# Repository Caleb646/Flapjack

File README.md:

# 🥞 Flapjack

Flapjack is a **VTOL drone platform** built from the ground up — custom **airframe**, **PCB**, and **firmware**.
---

## Features

- **Custom Flight Controller PCB**
    - STM32 microcontroller
    - IMU (SPI), barometer, GPS, and compass
    - Servo and ESC outputs

- **Firmware**
    - Python GUI for flight data
    - Real-time flight control loop
    - Sensor fusion (IMU + barometer + compass)
    - PID control
    - PID Mixing for tilt-thrust VTOL (motor + servo)

- **Airframe**
    - Dual-motor VTOL design with tilt servos
    - Lightweight and modular construction
    - Designed for hover-to-cruise transitions

---

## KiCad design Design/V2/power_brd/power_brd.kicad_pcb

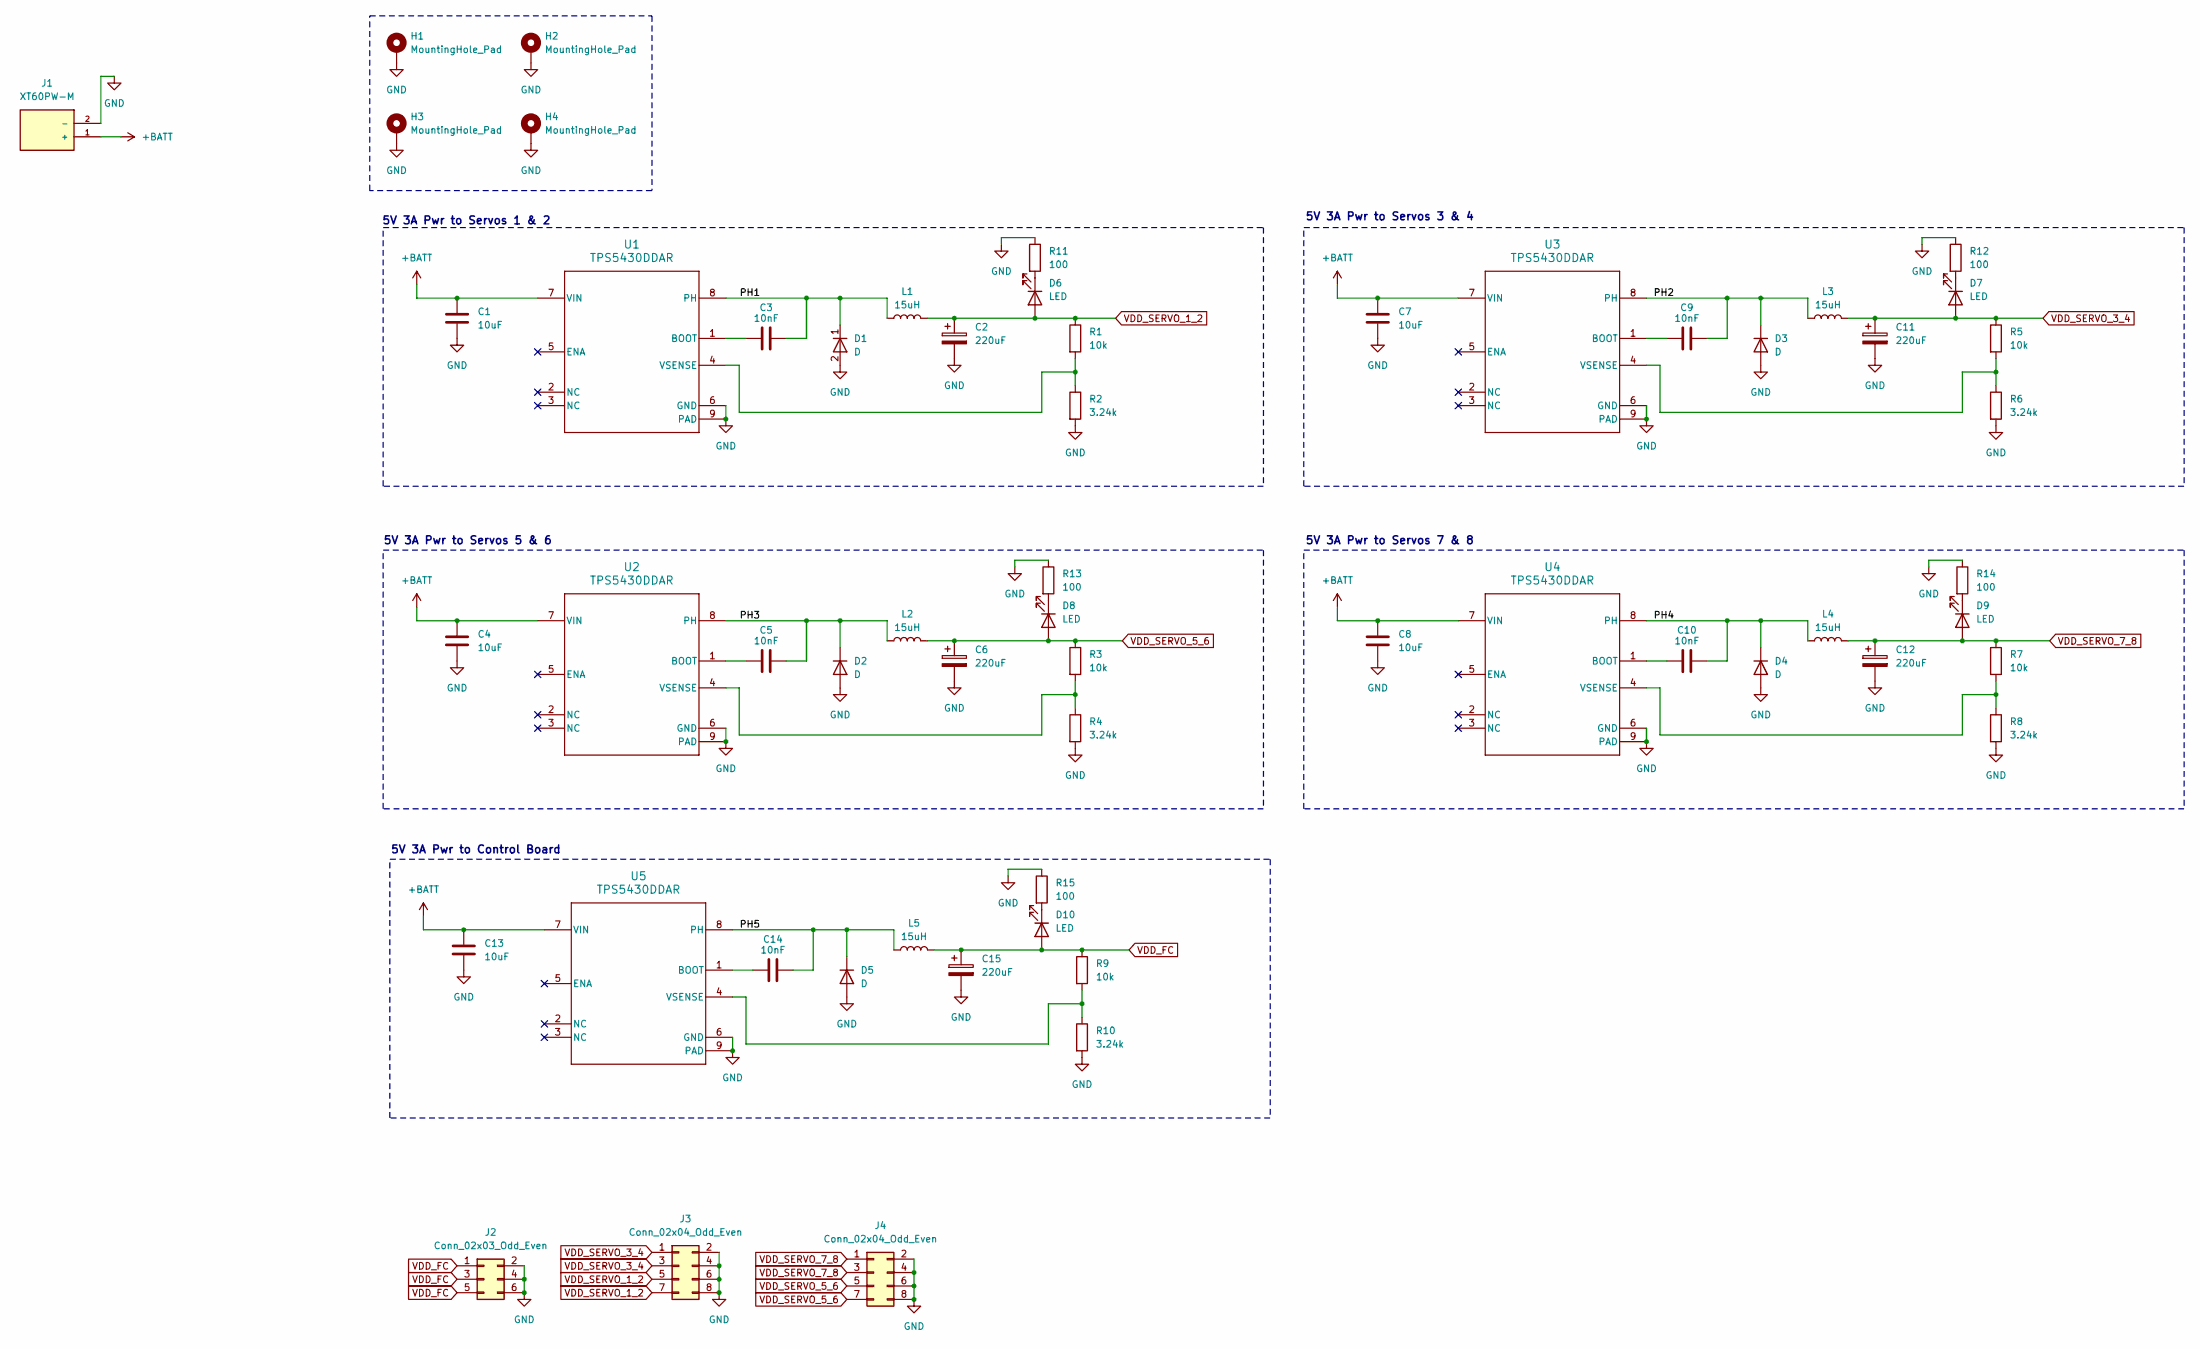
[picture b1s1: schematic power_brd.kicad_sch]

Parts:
C1, C4, C7, C8, C13: 10uF; C_1206_3216Metric_Pad1.33x1.80mm_HandSolder; LCSC Part # C13585
C2, C6, C11, C12, C15: 220uF; 10TPE220ML; LCSC Part # C147767
C3, C5, C9, C10, C14: 10nF; C_0805_2012Metric_Pad1.18x1.45mm_HandSolder; LCSC Part # C1710
D1, D2, D3, D4, D5: D; SMA_L4.3-W2.6-LS5.2-RD; LCSC Part # C8678
D6, D7, D8, D9, D10: LED; LED_0805_2012Metric_Pad1.15x1.40mm_HandSolder; LCSC Part # C84256
H1, H2, H3, H4: MountingHole_Pad; MountingHole_3.2mm_M3_Pad_Via
J1: XT60PW-M
J2: Conn_02x03_Odd_Even; PinHeader_2x03_P2.54mm_Vertical
J3, J4: Conn_02x04_Odd_Even; PinHeader_2x04_P2.54mm_Vertical
L1, L2, L3, L4, L5: 15uH; IND-SMD_L7.1-W6.6; LCSC Part # C22463824
R1, R3, R5, R7, R9: 10k; R_0805_2012Metric_Pad1.20x1.40mm_HandSolder; LCSC Part # C17414
R2, R4, R6, R8, R10: 3.24k; R_0805_2012Metric_Pad1.20x1.40mm_HandSolder; LCSC Part # C17609
R11, R12, R13, R14, R15: 100; R_0805_2012Metric_Pad1.20x1.40mm_HandSolder; LCSC Part # C17408
U1, U2, U3, U4, U5: TPS5430DDAR; LCSC Part # C9864

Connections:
+BATT: C1.1, C4.1, C7.1, C8.1, C13.1, J1.1 (+), U1.7 (VIN), U2.7 (VIN), U3.7 (VIN), U4.7 (VIN), U5.7 (VIN)
/PH1: C3.2, D1.1 (K), L1.1, U1.8 (PH)
/PH2: C9.2, D3.1 (K), L3.1, U3.8 (PH)
/PH3: C5.2, D2.1 (K), L2.1, U2.8 (PH)
/PH4: C10.2, D4.1 (K), L4.1, U4.8 (PH)
/PH5: C14.2, D5.1 (K), L5.1, U5.8 (PH)
GND: C1.2, C2.2, C4.2, C6.2, C7.2, C8.2, C11.2, C12.2, C13.2, C15.2, D1.2 (A), D2.2 (A), D3.2 (A), D4.2 (A), D5.2 (A), H1.1, H2.1, H3.1, H4.1, J1.2 (-), J2.2, J2.4, J2.6, J3.2, J3.4, J3.6, J3.8, J4.2, J4.4, J4.6, J4.8, R2.2, R4.2, R6.2, R8.2, R10.2, R11.1, R12.1, R13.1, R14.1, R15.1, U1.6 (GND), U1.9 (PAD), U2.6 (GND), U2.9 (PAD), U3.6 (GND), U3.9 (PAD), U4.6 (GND), U4.9 (PAD), U5.6 (GND), U5.9 (PAD)
unnamed: D6.1 (K), R11.2
unnamed: D7.1 (K), R12.2
unnamed: D8.1 (K), R13.2
unnamed: D9.1 (K), R14.2
unnamed: D10.1 (K), R15.2
unnamed: C3.1, U1.1 (BOOT)
unnamed: R1.2, R2.1, U1.4 (VSENSE)
unnamed: C5.1, U2.1 (BOOT)
unnamed: R3.2, R4.1, U2.4 (VSENSE)
unnamed: C9.1, U3.1 (BOOT)
unnamed: R5.2, R6.1, U3.4 (VSENSE)
unnamed: C10.1, U4.1 (BOOT)
unnamed: R7.2, R8.1, U4.4 (VSENSE)
unnamed: C14.1, U5.1 (BOOT)
unnamed: R9.2, R10.1, U5.4 (VSENSE)
VDD_FC: C15.1, D10.2 (A), J2.1, J2.3, J2.5, L5.2, R9.1
VDD_SERVO_1_2: C2.1, D6.2 (A), J3.5, J3.7, L1.2, R1.1
VDD_SERVO_3_4: C11.1, D7.2 (A), J3.1, J3.3, L3.2, R5.1
VDD_SERVO_5_6: C6.1, D8.2 (A), J4.5, J4.7, L2.2, R3.1
VDD_SERVO_7_8: C12.1, D9.2 (A), J4.1, J4.3, L4.2, R7.1

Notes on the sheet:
5V 3A Pwr to Servos 3 & 4
5V 3A Pwr to Servos 7 & 8
5V 3A Pwr to Servos 5 & 6
5V 3A Pwr to Servos 1 & 2
5V 3A Pwr to Control Board

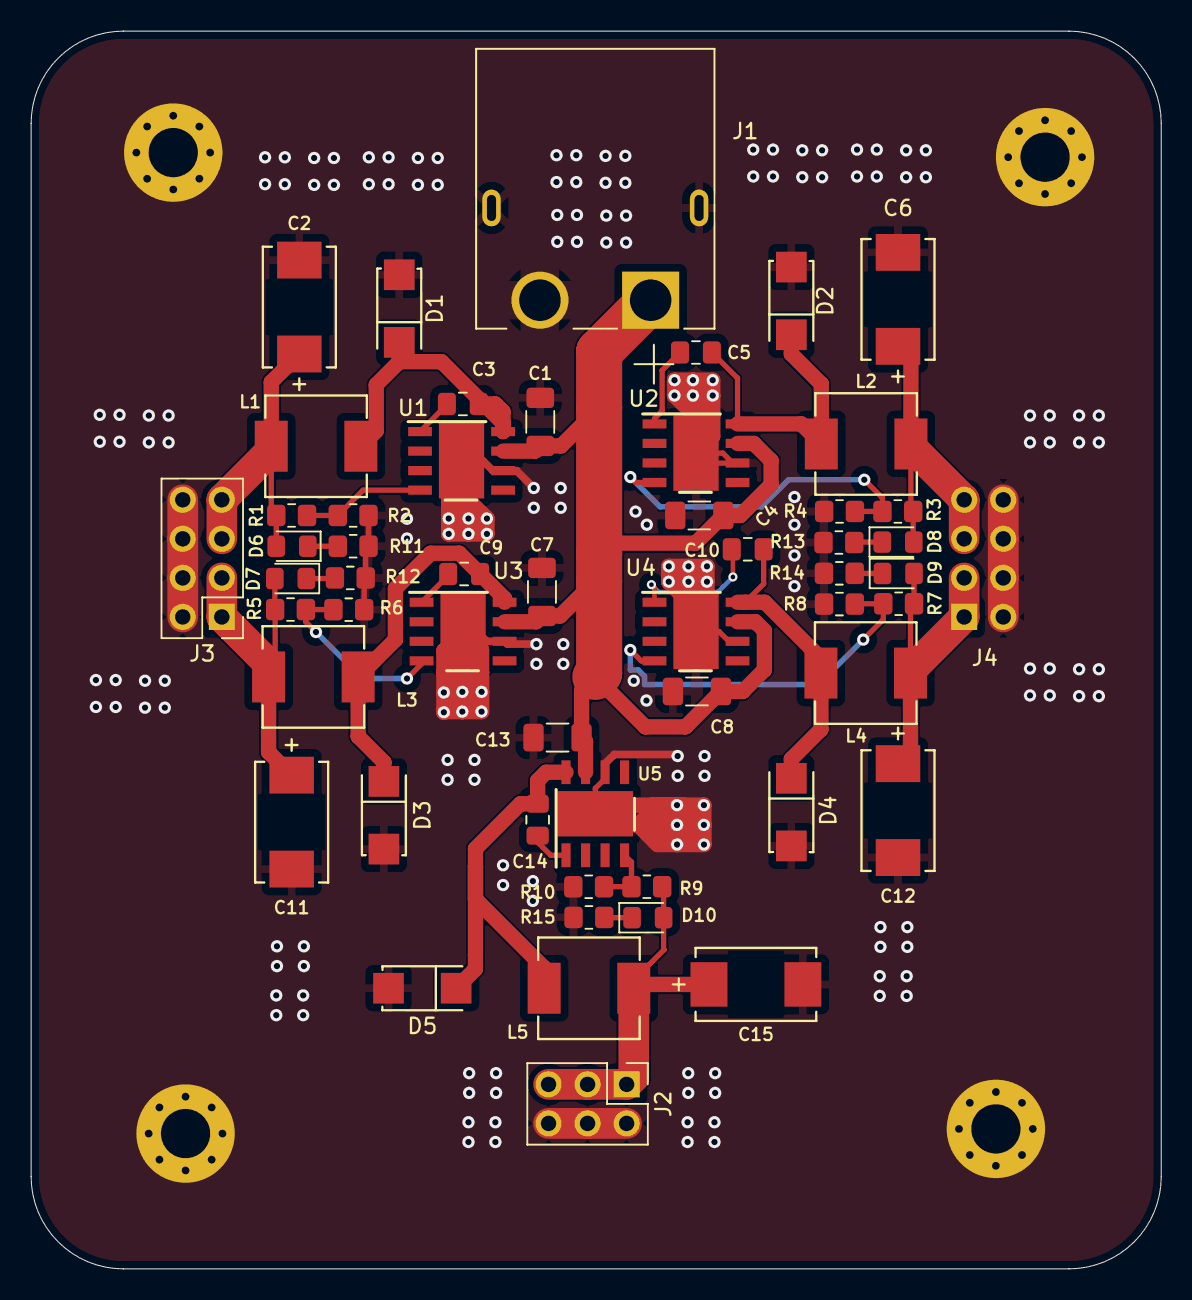
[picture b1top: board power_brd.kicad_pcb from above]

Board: 4 copper layers, 73.5 x 80.5 mm, 58 parts (1 on the bottom side), 27 nets.

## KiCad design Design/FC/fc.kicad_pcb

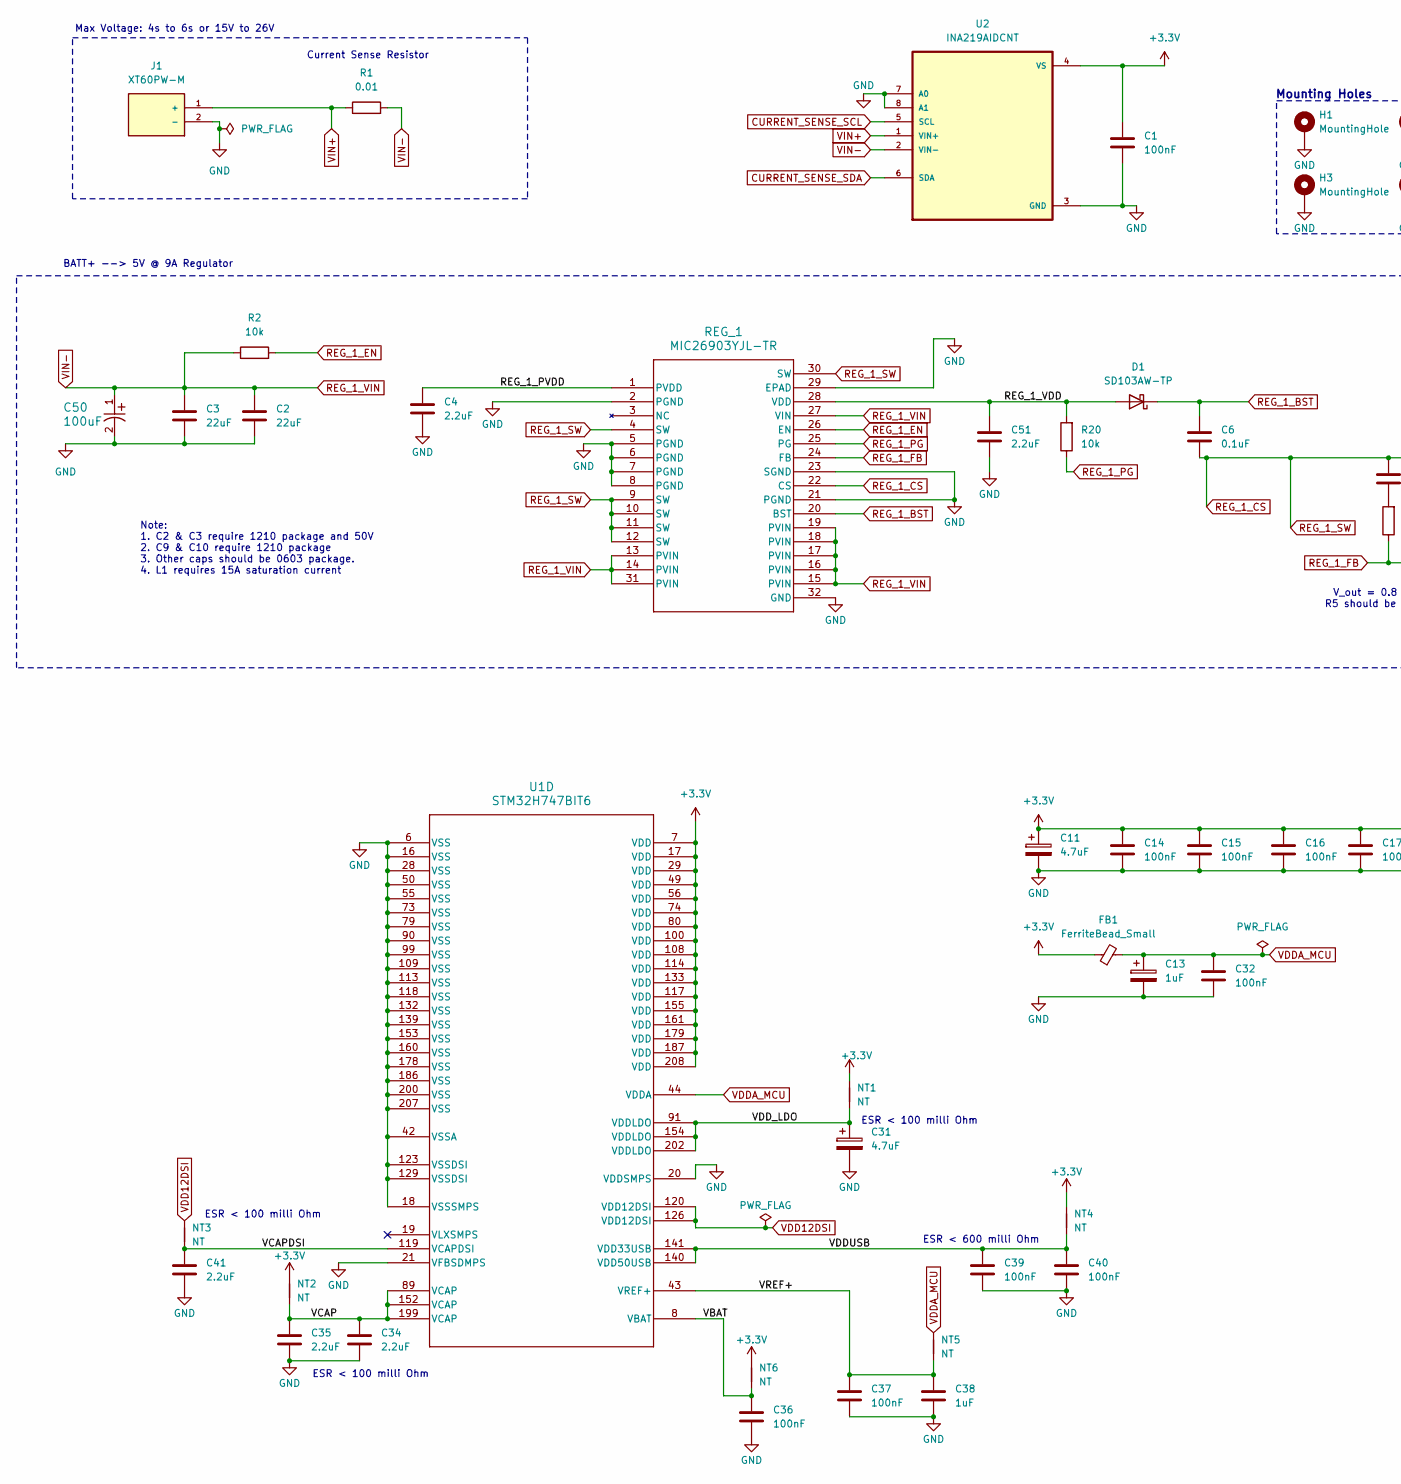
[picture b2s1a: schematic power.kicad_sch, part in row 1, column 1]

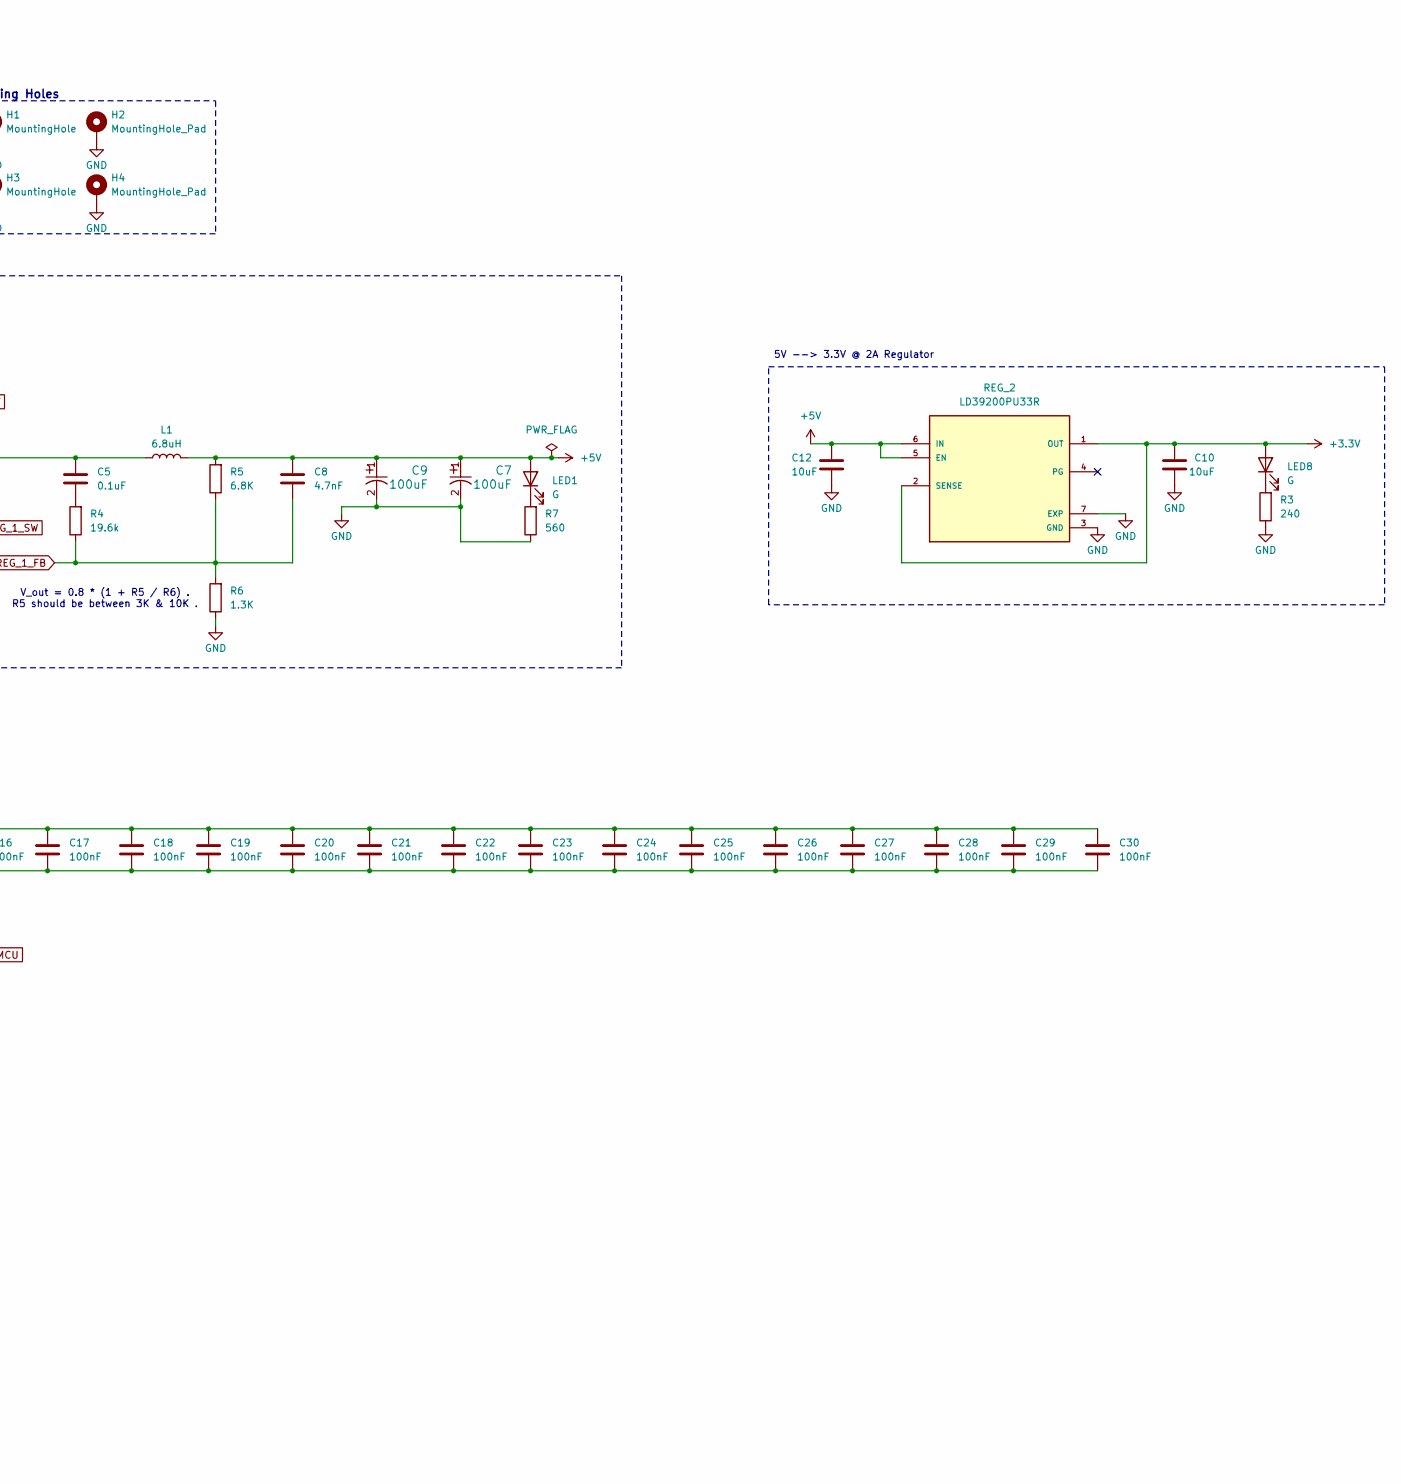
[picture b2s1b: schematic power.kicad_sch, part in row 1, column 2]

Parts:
C1, C14, C15, C16, C17, C18, C19, C20, C21, C22, C23, C24, C25, C26, C27, C28, C29, C30, C32, C36, C37, C39, C40: 100nF; C_0603_1608Metric_Pad1.08x0.95mm_HandSolder; Manufacturer_Part_Number CC0603KRX7R7BB104
C2, C3: 22uF; C_1210_3225Metric_Pad1.33x2.70mm_HandSolder; Manufacturer_Part_Number MSASG32MSB5226MPNA01
C4, C51: 2.2uF; C_0805_2012Metric_Pad1.18x1.45mm_HandSolder; Manufacturer_Part_Number UMK212BB7225KG-T
C5, C6: 0.1uF; C_0805_2012Metric_Pad1.18x1.45mm_HandSolder; Manufacturer_Part_Number KGM21NR71H104KT
C7, C9, C50: 100uF; CAP_6.3 X 7.7_PAN; Manufacturer_Part_Number EEE-FPV101XAP
C8: 4.7nF; C_0805_2012Metric_Pad1.18x1.45mm_HandSolder; Manufacturer_Part_Number C0805C472J3GEC7210
C10, C12: 10uF; C_0603_1608Metric_Pad1.08x0.95mm_HandSolder; Manufacturer_Part_Number GRM188R61E106KA73D
C11, C31: 4.7uF; C_0603_1608Metric_Pad1.08x0.95mm_HandSolder; Manufacturer_Part_Number GRM188R61E475KE11D
C13: 1uF; C_0603_1608Metric_Pad1.08x0.95mm_HandSolder; Manufacturer_Part_Number TACL105K016RTA
C34, C35, C41: 2.2uF; C_0603_1608Metric_Pad1.08x0.95mm_HandSolder; Manufacturer_Part_Number TMK107ABJ225KA-T
C38: 1uF; C_0603_1608Metric_Pad1.08x0.95mm_HandSolder; Manufacturer_Part_Number GRM188R61A105KA61D
D1: SD103AW-TP; Nexperia_CFP3_SOD-123W; Manufacturer_Part_Number SD103AW-TP
FB1: FerriteBead_Small; MPZ1005S121HT000; Manufacturer_Part_Number MPZ1005S121HT000
H1, H3: MountingHole; MountingHole_3.2mm_M3_Pad_Via
H2, H4: MountingHole_Pad; MountingHole_3.2mm_M3_Pad_Via
J1: XT60PW-M; PARTREV V1.2
L1: 6.8uH; IND_SRP1265A-6R8M_BRN; Manufacturer_Part_Number SRP1265A-6R8M
LED1, LED8: G; LED_0603_1608Metric; Manufacturer_Part_Number 5990081007F
NT1, NT2, NT3, NT4, NT5, NT6: NT; NetTie-2_SMD_Track0.35mm
R1: 0.01; RES_PE2512_YAG
R2, R20: 10k; RES_ERJ-T06J103V_0805
R3: 240; R_0603_1608Metric_Pad0.98x0.95mm_HandSolder
R4: 19.6k; RES_ERJ-PB6B1962V_0805
R5: 6.8K; R_0805_2012Metric_Pad1.20x1.40mm_HandSolder
R6: 1.3K; R_0805_2012Metric_Pad1.20x1.40mm_HandSolder
R7: 560; R_0603_1608Metric_Pad0.98x0.95mm_HandSolder
REG_1: MIC26903YJL-TR; MIC26903YJL-TR-MLF28_5X6_MCH
REG_2: LD39200PU33R; SON95P300X300X100-7N; PARTREV 3
U1: STM32H747BIT6; STM32H747BIT6-LQFP-208
U2: INA219AIDCNT; INA219AIDCNT-SOT65P280X145-8N

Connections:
+3.3V: C1.1, C10.1, C11.1, C14.1, C15.1, C16.1, C17.1, C18.1, C19.1, C20.1, C21.1, C22.1, C23.1, C24.1, C25.1, C26.1, C27.1, C28.1, C29.1, C30.1, FB1.1, LED8.2 (A), NT1.1, NT2.2, NT4.1, NT6.1, REG_2.1 (OUT), REG_2.2 (SENSE), U1.7 (VDD), U1.17 (VDD), U1.29 (VDD), U1.49 (VDD), U1.56 (VDD), U1.74 (VDD), U1.80 (VDD), U1.100 (VDD), U1.108 (VDD), U1.114 (VDD), U1.117 (VDD), U1.133 (VDD), U1.155 (VDD), U1.161 (VDD), U1.179 (VDD), U1.187 (VDD), U1.208 (VDD), U2.4 (VS); also elsewhere on the board
+5V: C7.1, C8.1, C9.1, C12.1, L1.2, LED1.2 (A), R5.2, REG_2.5 (EN), REG_2.6 (IN); also elsewhere on the board
/Power/REG_1_PVDD: C4.1, REG_1.1 (PVDD)
/Power/REG_1_VDD: C51.1, D1.2 (A), R20.2, REG_1.28 (VDD)
/Power/VBAT: C36.1, NT6.2, U1.8 (VBAT)
/Power/VCAP: C34.1, C35.1, NT2.1, U1.89 (VCAP), U1.152 (VCAP), U1.199 (VCAP)
/Power/VCAPDSI: C41.1, NT3.1, U1.119 (VCAPDSI)
/Power/VDDUSB: C39.1, C40.1, NT4.2, U1.140 (VDD50USB), U1.141 (VDD33USB)
/Power/VDD_LDO: C31.1, NT1.2, U1.91 (VDDLDO), U1.154 (VDDLDO), U1.202 (VDDLDO)
/Power/VREF+: C37.1, C38.1, NT5.2, U1.43 (VREF+)
CURRENT_SENSE_SCL: U2.5 (SCL); also elsewhere on the board
CURRENT_SENSE_SDA: U2.6 (SDA); also elsewhere on the board
GND: C1.2, C2.2, C3.2, C4.2, C7.2, C9.2, C10.2, C11.2, C12.2, C13.2, C14.2, C15.2, C16.2, C17.2, C18.2, C19.2, C20.2, C21.2, C22.2, C23.2, C24.2, C25.2, C26.2, C27.2, C28.2, C29.2, C30.2, C31.2, C32.2, C34.2, C35.2, C36.2, C37.2, C38.2, C39.2, C40.2, C41.2, C50.2, C51.2, H1.1, H2.1, H3.1, H4.1, J1.2 (-), R3.1, R6.1, R7.1, REG_1.2 (PGND), REG_1.5 (PGND), REG_1.6 (PGND), REG_1.7 (PGND), REG_1.8 (PGND), REG_1.21 (PGND), REG_1.23 (SGND), REG_1.29 (EPAD), REG_1.32 (GND), REG_2.3 (GND), REG_2.7 (EXP), U1.6 (VSS), U1.16 (VSS), U1.18 (VSSSMPS), U1.20 (VDDSMPS), U1.21 (VFBSDMPS), U1.28 (VSS), U1.42 (VSSA), U1.50 (VSS), U1.55 (VSS), U1.73 (VSS), U1.79 (VSS), U1.90 (VSS), U1.99 (VSS), U1.109 (VSS), U1.113 (VSS), U1.118 (VSS), U1.123 (VSSDSI), U1.129 (VSSDSI), U1.132 (VSS), U1.139 (VSS), U1.153 (VSS), U1.160 (VSS), U1.178 (VSS), U1.186 (VSS), U1.200 (VSS), U1.207 (VSS), U2.3 (GND), U2.7 (A0), U2.8 (A1); also elsewhere on the board
unnamed: C5.2, R4.2
unnamed: LED1.1 (K), R7.2
unnamed: LED8.1 (K), R3.2
REG_1_BST: C6.1, D1.1 (K), REG_1.20 (BST)
REG_1_CS: C5.1, C6.2, L1.1, REG_1.4 (SW), REG_1.9 (SW), REG_1.10 (SW), REG_1.11 (SW), REG_1.12 (SW), REG_1.22 (CS), REG_1.30 (SW)
REG_1_EN: R2.2, REG_1.26 (EN)
REG_1_FB: C8.2, R4.1, R5.1, R6.2, REG_1.24 (FB)
REG_1_PG: R20.1, REG_1.25 (PG)
REG_1_VIN: C2.1, C3.1, C50.1, R1.2, R2.1, REG_1.13 (PVIN), REG_1.14 (PVIN), REG_1.15 (PVIN), REG_1.16 (PVIN), REG_1.17 (PVIN), REG_1.18 (PVIN), REG_1.19 (PVIN), REG_1.27 (VIN), REG_1.31 (PVIN), U2.2 (VIN-)
VDD12DSI: NT3.2, U1.120 (VDD12DSI), U1.126 (VDD12DSI)
VDDA_MCU: C13.1, C32.1, FB1.2, NT5.1, U1.44 (VDDA)
VIN+: J1.1 (+), R1.1, U2.1 (VIN+)

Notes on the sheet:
5V --> 3.3V @ 2A Regulator
Mounting Holes
V_out = 0.8 * (1 + R5 / R6) . R5 should be between 3K & 10K .
ESR < 100 milli Ohm
Max Voltage: 4s to 6s or 15V to 26V
BATT+ --> 5V @ 9A Regulator
ESR < 600 milli Ohm
Current Sense Resistor
Note: 1. C2 & C3 require 1210 package and 50V 2. C9 & C10 require 1210 package 3. Other caps should be 0603 package. 4. L1 requires 15A saturation current

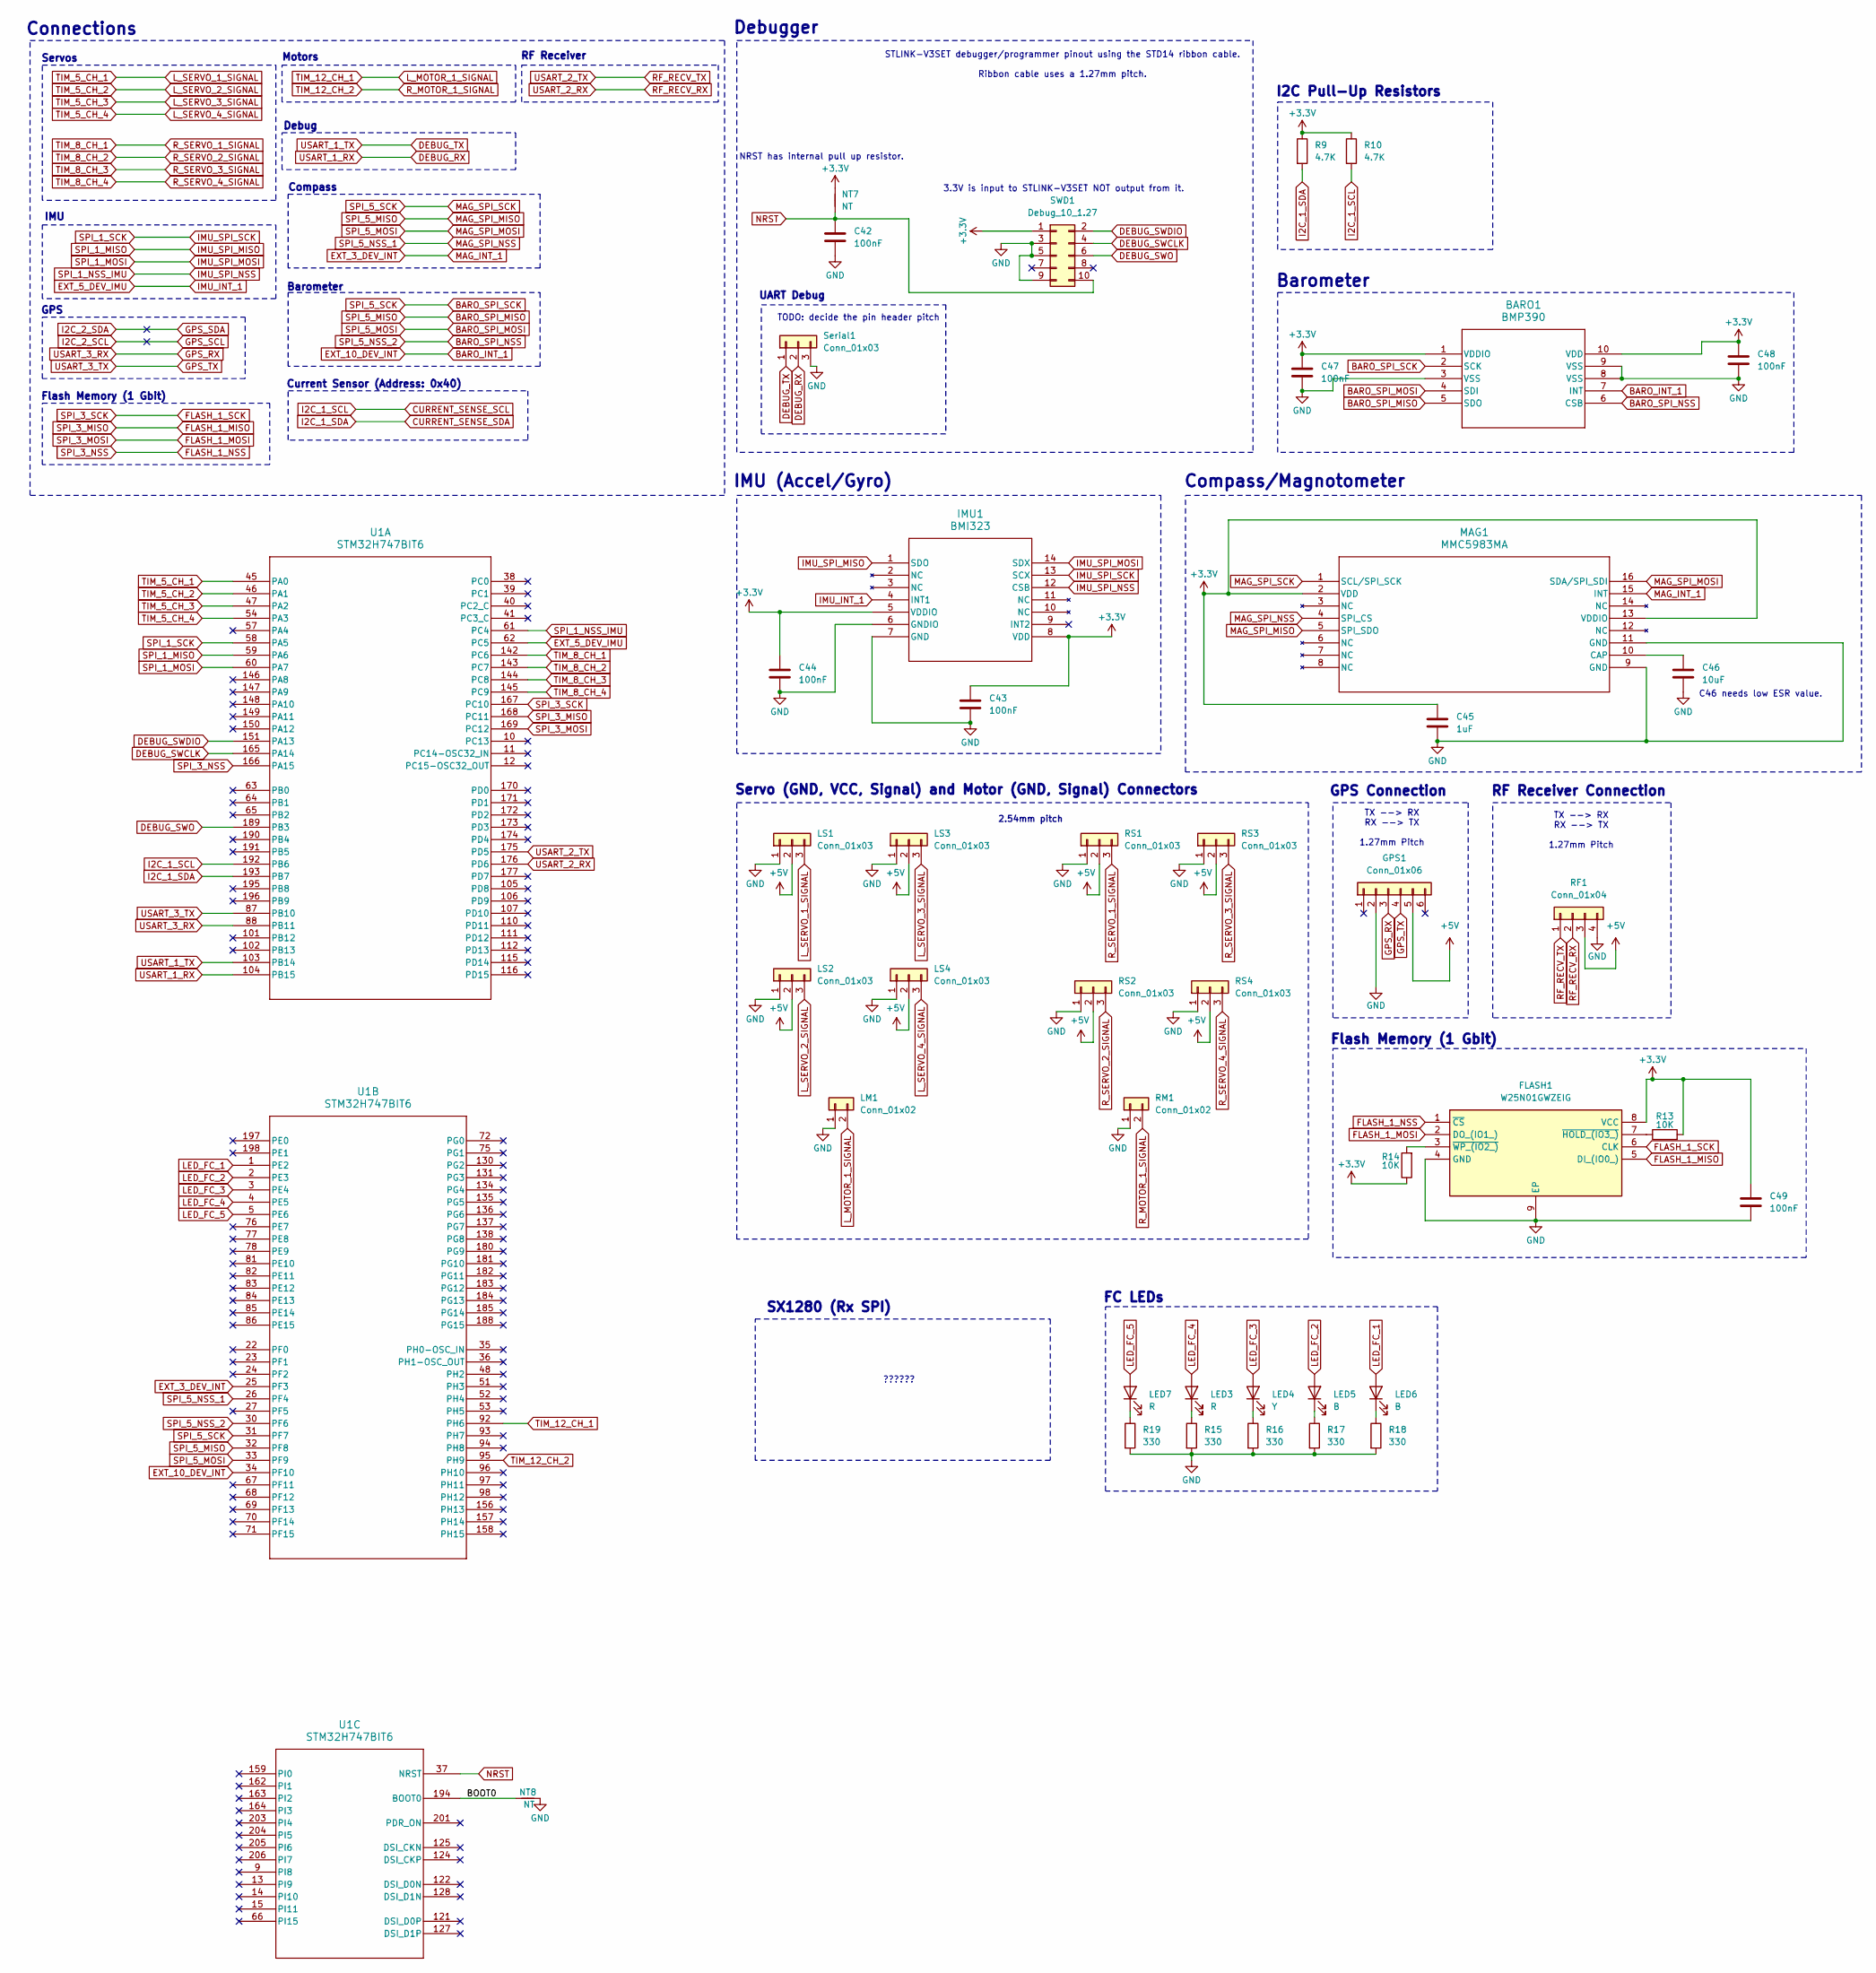
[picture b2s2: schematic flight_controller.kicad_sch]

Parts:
BARO1: BMP390; BMP390-10LGA_2X2X0p75_BOS; Manufacturer_Part_Number BMP390
C42, C43, C44, C47, C48, C49: 100nF; C_0603_1608Metric_Pad1.08x0.95mm_HandSolder; Manufacturer_Part_Number CC0603KRX7R7BB104
C45: 1uF; C_0603_1608Metric_Pad1.08x0.95mm_HandSolder; Manufacturer_Part_Number CL10B105KO8NNNC
C46: 10uF; C_0805_2012Metric_Pad1.18x1.45mm_HandSolder; Manufacturer_Part_Number C0805C106K8RACTU
FLASH1: W25N01GWZEIG; Mouser Part Number 454-W25N01GWZEIG
GPS1: Conn_01x06; CONN_532610001-SD_06Pin_1.25mm; Manufacturer_Part_Number 0532610671
IMU1: BMI323; BMI323_BOS; Manufacturer_Part_Number BMI323
LED3, LED7: R; LED_0603_1608Metric; Manufacturer_Part_Number LTST-C191KRKT
LED4: Y; LED_0603_1608Metric; Manufacturer_Part_Number LTST-C191KSKT
LED5, LED6: B; LED_0603_1608Metric; Manufacturer_Part_Number LTST-C193TBKT-5A
LM1: Conn_01x02; PinHeader_2x01_P2.54mm_Vertical; Manufacturer_Part_Number B2B-XH-A
LS1, LS2, LS3, LS4: Conn_01x03; PinHeader_1x03_P2.54mm_Vertical; Manufacturer_Part_Number B3B-XH-A
MAG1: MMC5983MA; MMC5983MA_MEM; Manufacturer_Part_Number MMC5983MA
NT7, NT8: NT; NetTie-2_SMD_Track0.35mm
R9, R10: 4.7K; R_0603_1608Metric_Pad0.98x0.95mm_HandSolder; Manufacturer_Part_Number CRGP0603F4K7
R13, R14: 10K; R_0603_1608Metric_Pad0.98x0.95mm_HandSolder; Manufacturer_Part_Number CRGP0603F10K
R15, R16, R17, R18, R19: 330; R_0603_1608Metric_Pad0.98x0.95mm_HandSolder; Manufacturer_Part_Number CRGP0603F330R
RF1: Conn_01x04; CONN_532610471_SMD_4Pin_1.25mm
RM1: Conn_01x02; PinHeader_2x01_P2.54mm_Vertical; Manufacturer_Part_Number B2B-XH-A
RS1, RS2, RS3, RS4: Conn_01x03; PinHeader_1x03_P2.54mm_Vertical; Manufacturer_Part_Number B3B-XH-A
SWD1: Debug_10_1.27; CONN_GRPB052VWQS-RC_OddEven_2x5Pins_1.27mm; Manufacturer_Part_Number GRPB052VWQS-RC
Serial1: Conn_01x03; PinHeader_1x03_P2.54mm_Vertical; Manufacturer_Part_Number B3B-XH-A
U1: STM32H747BIT6; STM32H747BIT6-LQFP-208; Manufacturer_Part_Number STM32H747BIT6

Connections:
+3.3V: BARO1.1 (VDDIO), BARO1.10 (VDD), C43.1, C44.1, C45.1, C47.1, C48.1, C49.1, FLASH1.8 (VCC), IMU1.5 (VDDIO), IMU1.8 (VDD), MAG1.2 (VDD), MAG1.13 (VDDIO), NT7.1, R9.1, R10.1, R13.2, R14.1, SWD1.1; also elsewhere on the board
+5V: GPS1.5, LS1.2, LS2.2, LS3.2, LS4.2, RF1.3, RS1.2, RS2.2, RS3.2, RS4.2; also elsewhere on the board
/Flight Controller/BOOT0: NT8.1, U1.194 (BOOT0)
BARO_INT_1: BARO1.7 (INT), U1.34 (PF10)
BARO_SPI_MISO: BARO1.5 (SDO), MAG1.5 (SPI_SDO), U1.32 (PF8)
BARO_SPI_MOSI: BARO1.4 (SDI), MAG1.16 (SDA/SPI_SDI), U1.33 (PF9)
BARO_SPI_NSS: BARO1.6 (CSB), U1.30 (PF6)
BARO_SPI_SCK: BARO1.2 (SCK), MAG1.1 (SCL/SPI_SCK), U1.31 (PF7)
CURRENT_SENSE_SCL: R10.2, U1.192 (PB6); also elsewhere on the board
CURRENT_SENSE_SDA: R9.2, U1.193 (PB7); also elsewhere on the board
DEBUG_RX: Serial1.2, U1.104 (PB15)
DEBUG_SWCLK: SWD1.4, U1.165 (PA14)
DEBUG_SWDIO: SWD1.2, U1.151 (PA13)
DEBUG_SWO: SWD1.6, U1.189 (PB3)
DEBUG_TX: Serial1.1, U1.103 (PB14)
EXT_3_DEV_INT: MAG1.15 (INT), U1.25 (PF3)
EXT_5_DEV_IMU: IMU1.4 (INT1), U1.62 (PC5)
FLASH_1_MISO: FLASH1.5 (DI_(IO0_)), U1.168 (PC11)
FLASH_1_MOSI: FLASH1.2 (DO_(IO1_)), U1.169 (PC12)
FLASH_1_NSS: FLASH1.1 (~CS), U1.166 (PA15)
FLASH_1_SCK: FLASH1.6 (CLK), U1.167 (PC10)
GND: BARO1.3 (VSS), BARO1.8 (VSS), BARO1.9 (VSS), C42.2, C43.2, C44.2, C45.2, C46.2, C47.2, C48.2, C49.2, FLASH1.4 (GND), FLASH1.9 (EP), GPS1.2, IMU1.6 (GNDIO), IMU1.7 (GND), LM1.1, LS1.1, LS2.1, LS3.1, LS4.1, MAG1.9 (GND), MAG1.11 (GND), NT8.2, R15.2, R16.2, R17.2, R18.2, R19.2, RF1.4, RM1.1, RS1.1, RS2.1, RS3.1, RS4.1, SWD1.3, SWD1.5, SWD1.9, Serial1.3; also elsewhere on the board
GPS_RX: GPS1.3, U1.88 (PB11)
GPS_TX: GPS1.4, U1.87 (PB10)
IMU_SPI_MISO: IMU1.1 (SDO), U1.59 (PA6)
IMU_SPI_MOSI: IMU1.14 (SDX), U1.60 (PA7)
IMU_SPI_NSS: IMU1.12 (CSB), U1.61 (PC4)
IMU_SPI_SCK: IMU1.13 (SCX), U1.58 (PA5)
LED_FC_1: LED6.2 (A), U1.1 (PE2)
LED_FC_2: LED5.2 (A), U1.2 (PE3)
LED_FC_3: LED4.2 (A), U1.3 (PE4)
LED_FC_4: LED3.2 (A), U1.4 (PE5)
LED_FC_5: LED7.2 (A), U1.5 (PE6)
L_MOTOR_1_SIGNAL: LM1.2, U1.92 (PH6)
L_SERVO_1_SIGNAL: LS1.3, U1.45 (PA0)
L_SERVO_2_SIGNAL: LS2.3, U1.46 (PA1)
L_SERVO_3_SIGNAL: LS3.3, U1.47 (PA2)
L_SERVO_4_SIGNAL: LS4.3, U1.54 (PA3)
MAG_SPI_NSS: MAG1.4 (SPI_CS), U1.26 (PF4)
NRST: C42.1, NT7.2, SWD1.10, U1.37 (NRST)
unnamed: FLASH1.7 (~HOLD_(IO3_)), R13.1
unnamed: FLASH1.3 (~WP_(IO2_)), R14.2
unnamed: LED3.1 (K), R15.1
unnamed: LED4.1 (K), R16.1
unnamed: LED5.1 (K), R17.1
unnamed: LED6.1 (K), R18.1
unnamed: LED7.1 (K), R19.1
unnamed: C46.1, MAG1.10 (CAP)
RF_RECV_RX: RF1.2, U1.176 (PD6)
RF_RECV_TX: RF1.1, U1.175 (PD5)
R_MOTOR_1_SIGNAL: RM1.2, U1.95 (PH9)
R_SERVO_1_SIGNAL: RS1.3, U1.142 (PC6)
R_SERVO_2_SIGNAL: RS2.3, U1.143 (PC7)
R_SERVO_3_SIGNAL: RS3.3, U1.144 (PC8)
R_SERVO_4_SIGNAL: RS4.3, U1.145 (PC9)

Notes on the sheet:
RF Receiver
TX --> RX RX --> TX 1.27mm Pitch
Connections
2.54mm pitch
UART Debug
3.3V is input to STLINK-V3SET NOT output from it.
GPS Connection
RF Receiver Connection
GPS
I2C Pull-Up Resistors
NRST has internal pull up resistor.
Current Sensor (Address: 0x40)
Compass
SX1280 (Rx SPI)
Debugger
Flash Memory (1 Gbit)
TODO: decide the pin header pitch
IMU (Accel/Gyro)
C46 needs low ESR value.
Motors
Servos
IMU
Compass/Magnotometer
??????
Servo (GND, VCC, Signal) and Motor (GND, Signal) Connectors
Barometer
STLINK-V3SET debugger/programmer pinout using the STD14 ribbon cable. Ribbon cable uses a 1.27mm pitch.
Debug
FC LEDs
